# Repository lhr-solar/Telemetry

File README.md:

# Telemetry
Legacy Telemetry Code from BeVolt. Some of this might be useful as a reference for development of future telemetry systems.

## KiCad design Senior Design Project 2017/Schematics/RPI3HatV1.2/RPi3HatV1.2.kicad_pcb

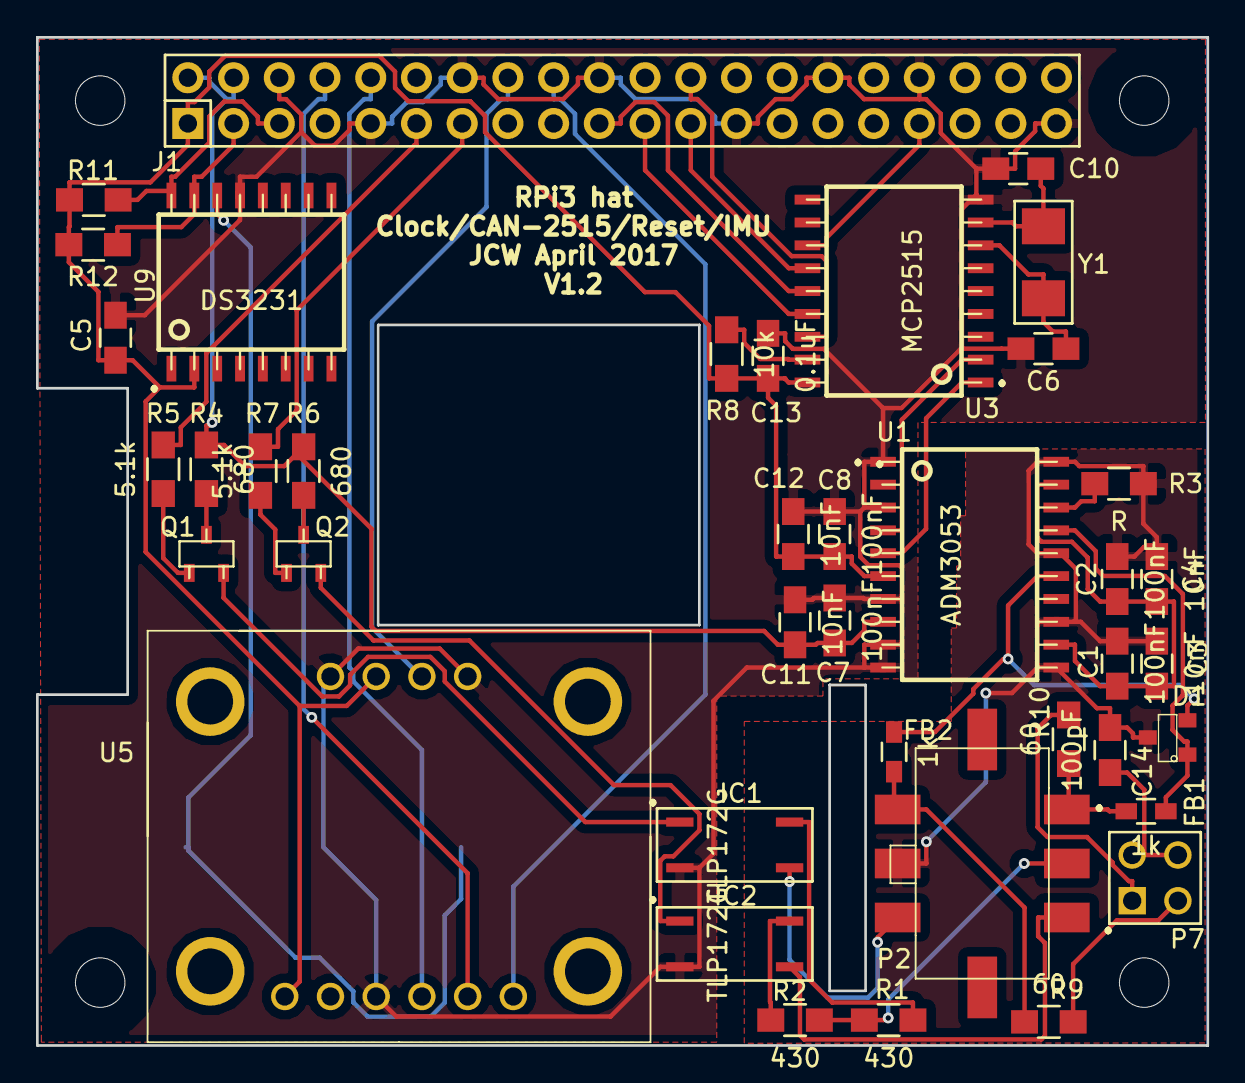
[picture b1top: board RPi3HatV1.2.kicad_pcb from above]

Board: 2 copper layers, 65.0 x 56.0 mm, 45 parts (1 on the bottom side), 43 nets.

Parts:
BAT1: BK-916BattHold1220; BK-916BatClip1220
C1, C2, C7, C8: 100nF; C_0805_HandSoldering
C3, C4, C11, C12: 10nF; C_0805_HandSoldering
C5, C13: 0.1uF; C_0805_HandSoldering
C6, C10: 20pF; C_0805_HandSoldering
C14: 100pF; C_0805_HandSoldering
D1: NUP2105L; SOT23-1700
FB1, FB2: 1k; R_0603_HandSoldering
H1, H2, H3, H4: MountingHole; RPi_Hat_Mounting_Hole
IC1, IC2: TLP172G; 2.54SOP4
J1: RPi_GPIO_header; Pin_Header_Straight_2x20
P2: 43045-0620; 43045-0620header6pin
P7: optional termination; pin_array_2x02
Q1, Q2: 2N3904; sot23_b
R1, R2: 430; R_0805_HandSoldering
R3: R; R_0805_HandSoldering
R4, R6: 680; R_0805_HandSoldering
R5, R7: 5.1k; R_0805_HandSoldering
R8, R11, R12: 10k; R_0805_HandSoldering
R9, R10: 60; R_0805_HandSoldering
U1: ADM3053; soic-20
U3: MCP2515; soic-18
U5: AdafruitBNO055; BDO055BOB
U9: DS3231; soic-16
Y1: 16MHz; 2SMD

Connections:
+3V3: C5.2, C8.1, C12.1, C13.1, J1.1, R8.1, R11.1, R12.1, U1.6, U3.18, U5.1, U5.10, U9.2
+5C: P2.2, R1.1, R2.2
+5V: C7.1, C11.1, J1.2, J1.4, R4.2, R6.2, U1.8
/BNO055int: J1.16, U5.9
/BNO055rst: J1.18, U5.6
/CANH: FB1.1, P2.1, R10.2
/CANL: FB2.1, P2.4, R9.2
/SPIint: J1.33, U3.12
/STM1rst: J1.11, R5.1
/STM2rst: J1.13, R7.1
/reset1: IC1.3, P2.6
/reset2: IC2.3, P2.3
GND: BAT1.2, C5.1, C6.2, C7.2, C8.2, C10.2, C11.2, C12.2, C13.2, IC1.2, IC2.2, J1.6, J1.9, J1.14, J1.20, J1.25, J1.30, J1.34, J1.39, U1.1, U1.3, U1.7, U1.9, U1.10, U3.9, U5.3, U5.8, U5.11, U9.13
GNDREF: C1.2, C2.2, C3.2, C4.2, C14.1, D1.3, P2.5, R3.2, U1.11, U1.13, U1.16, U1.20
unnamed: BAT1.1, BAT1.3, U9.14
unnamed: C1.1, C2.1, C3.1, C4.1, U1.12, U1.19
unnamed: C6.1, U3.7, Y1.1
unnamed: C10.1, U3.8, Y1.2
unnamed: C14.2, P7.2, P7.4
unnamed: D1.1, FB1.2, U1.17
unnamed: D1.2, FB2.2, U1.15
unnamed: IC1.1, Q1.3
unnamed: IC1.4, R1.2
unnamed: IC2.1, Q2.3
unnamed: IC2.4, R2.1
unnamed: J1.3, R12.2, U9.15
unnamed: J1.5, R11.2, U9.16
unnamed: J1.8, U5.5
unnamed: J1.10, U5.4
unnamed: J1.19, U3.14
unnamed: J1.21, U3.15
unnamed: J1.23, U3.13
unnamed: J1.24, U3.16
unnamed: P7.1, R10.1
unnamed: P7.3, R9.1
unnamed: Q1.1, R4.1
unnamed: Q1.2, R5.2
unnamed: Q2.1, R6.1
unnamed: Q2.2, R7.2
unnamed: R3.1, U1.18
unnamed: R8.2, U3.17
unnamed: U1.4, U3.2
unnamed: U1.5, U3.1

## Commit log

2019-02-08 Deleted Files
2019-02-08 Added all material for current system
2019-09-18 add RP3 demo folder
    readme to set up influx + grafana and a small python program to generate dummy data to send into the system
2019-09-21 Added files for raspberry pi telemtry server project. Also added a Readme that describes how to set up and run the system.
2019-09-28 Updated readme and added compiled binary file for nucleo
2019-09-28 updated readme again
2019-09-28 Updated start script to fix time difference issue with grafana server
2019-09-28 update comment to reflect actual code
2019-09-28 updated comments of main.cpp
2019-09-28 Updated startup script
2019-10-12 update datagen and start script
2019-10-12 add instructions on how to etch completed image
2019-11-02 Added python file for web scraping, updated the start up script to use this file instead of the udp socket file
2019-11-23 updated parsing of webpage to parse the whole page. Changed code for webscraping but it is not working yet. Not sure if this is an issue with the raspberry pi system or the telemetry system on the nu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
2019-11-23 basically got system working with senior design system. There is a bug where if the selenium browser is closed the pullTelData script will run infinetly and can't be stopped with ctrl c.
2019-12-07 added chromedriver that is used for web scraping
2019-12-07 updated pullTelData startTelemetry and telemetryStop to all work correctly without needing to be moved out of the git repo directory
2019-12-07 Added old version of startTelemetry script so it can be used with the old udp system
2019-12-07 Updated readme with instructions for the new system
    The new system uses web scraping instead of udp streaming.
2019-12-07 Fixed spelling and updated wifi setup instructions
2019-12-08 Changed file to reflect that it stops the web scraper and no longer stops the socket
2019-12-08 Updated old comment
2019-12-08 Updated readme to tell user to pull from git before running anything
2019-12-18 Update Readme.md
    Updated password for grafana server
2020-03-07 `vallen` is verified to be less than `len`, therefore, it can never be the case that `vallen >= len + sizeof(rhostname)`.
    This PR fixes the check so the `rhostname` array does not overflow.
    Reported-by: Github Security Lab <securitylab@github.com>
2020-10-03 Add License
